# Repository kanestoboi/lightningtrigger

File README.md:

# Lightning Trigger

Features
* Lightning Triggering - By using a photo transistor, lightning strikes are detected and triggers the camera at the same instant.  
  
* Sound Triggering - Sound triggering mode is used to capture sound events such as water droplets, breaking glass, and fireworks.  
  
* Timelapse- Calculates the number of photos for a given length timelapse, given the photo duration, interval, and total timelapse length before taking all the required photos.  
  
Currently has support for two triggering outputs (can trigger two devices at once) with an additional two outputs being added in the next revision.  
  
Control is through an Android app using the HM-11 Bluetooth module.  
  
Power is from a li-po battery and is charged using an onboard li-po charger.

## Images

Images are located in the [Images](https://github.com/kanestoboi/lightningtrigger/tree/master/Images) directory.

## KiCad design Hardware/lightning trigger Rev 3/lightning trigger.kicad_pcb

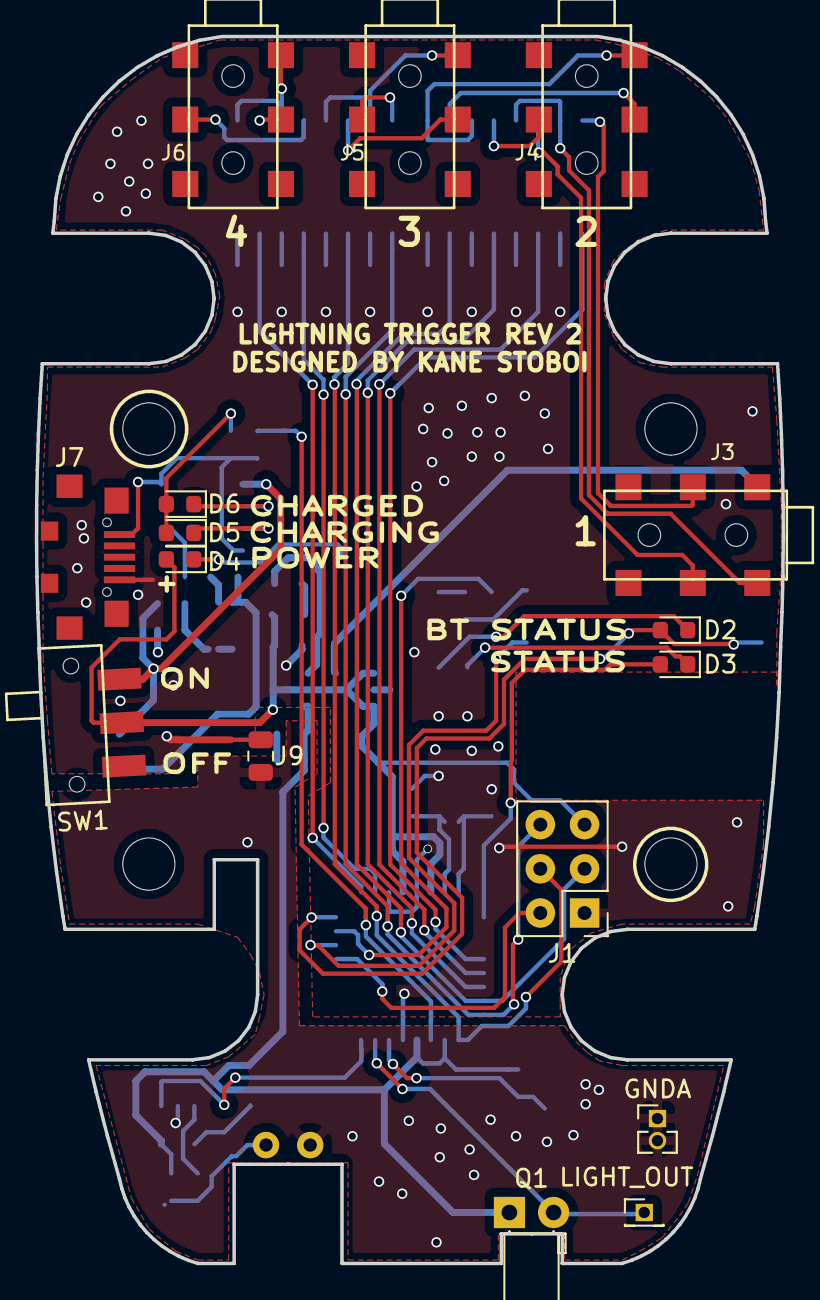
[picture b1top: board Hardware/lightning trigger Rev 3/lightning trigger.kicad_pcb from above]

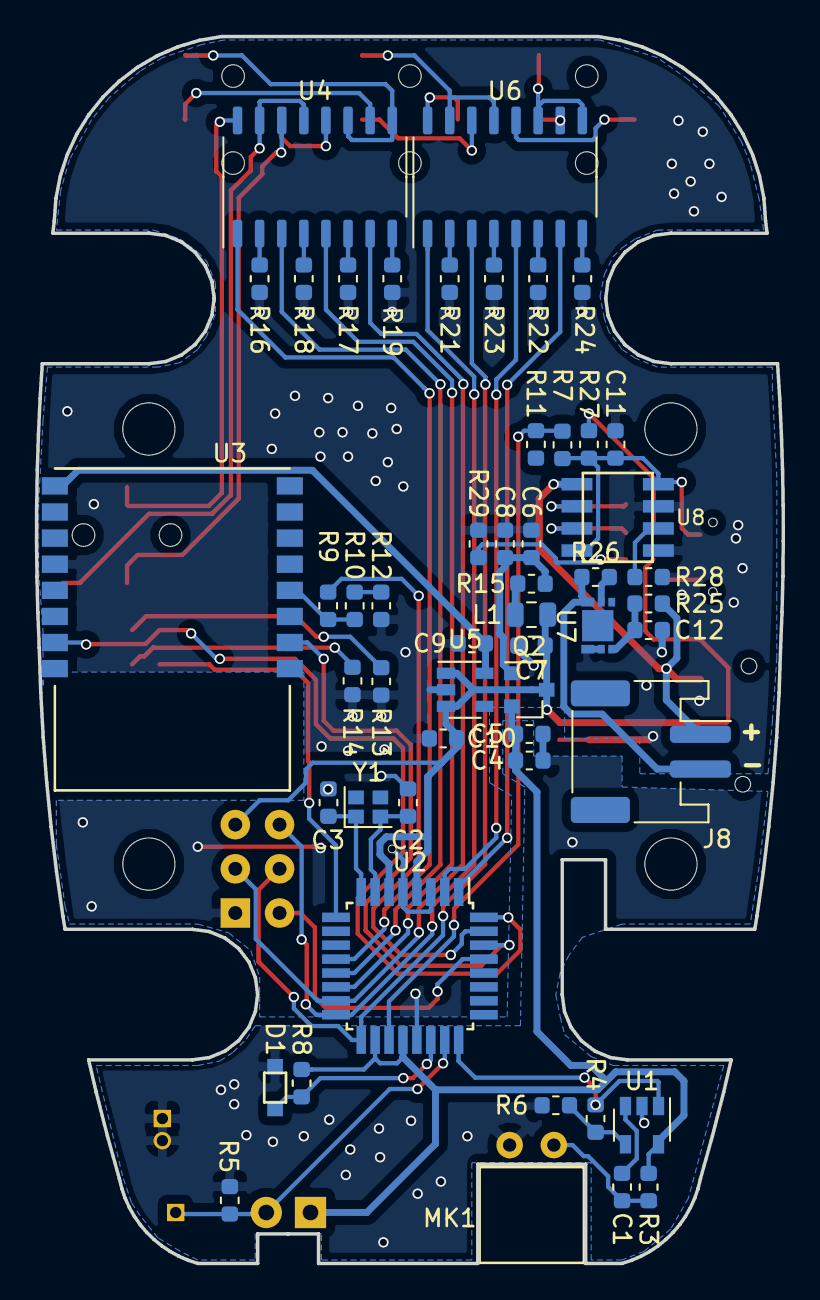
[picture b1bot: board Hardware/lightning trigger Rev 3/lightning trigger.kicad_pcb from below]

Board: 2 copper layers, 42.9 x 70.5 mm, 68 parts (52 on the bottom side), 63 nets.

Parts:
C1, C4, C7, C8, C9, C10, C11, C12: 100nF; C_0603_1608Metric
C2: 10pF; C_0603_1608Metric
C3: 22pF; C_0603_1608Metric
C5, C6: 1nF; C_0603_1608Metric
D1: D_Zener; SC-90A
D2, D3, D4, D5, D6: LED; LED_0603_1608Metric
GNDA: PinHeader_1x02_P1.27mm_Vertical
J1: Conn_02x03_Odd_Even; Pin_Header_Straight_2x03_Pitch2.54mm
J3, J4, J5, J6: SJ-2523-SMT; PJ-237-6A
J7: USB_OTG; USB_Micro_C77238
J8: Conn_01x02_Female; JST_PH_S2B-PH-SM4-TB_1x02-1MP_P2.00mm_Horizontal
J9: Conn_01x02; R_0805_2012Metric
L1: Ferrite_Bead; C_0805_2012Metric
LIGHT_OUT: PinHeader_1x01_P1.27mm_Vertical
MK1: Microphone; ELECTRET MICROPHONE
Q1: Q_Photo_NPN; LED_D3.0mm_Horizontal_O1.27mm_Z2.0mm
Q2: MMBT3904; SOT-23
R3, R5: 10k; R_0603_1608Metric
R4, R6, R16, R17, R18, R19, R21, R22, R23, R24, R25: 150; R_0603_1608Metric
R7, R9, R10, R11, R12, R13, R14, R26, R27, R28, R29: 2k; R_0603_1608Metric
R8: 47; R_0603_1608Metric
R15: 160k; R_0603_1608Metric
SW1: SW_SPDT; JS102011SAQN
U1: MCP6001; SOT-23-5
U2: ATMEGA328P-AU; TQFP-32_7x7mm_Pitch0.8mm
U3: HM-11
U4, U6: TLP291-4; SOIC-16_4.55x10.3mm_P1.27mm
U5: TLV70233_SOT23-5; SOT-23-5
U7: AP9211; U-DFN2030-6
U8: TP4056; SOP-8
Y1: Crystal; Crystal_SMD_2016-4Pin_2.0x1.6mm

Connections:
3.3V: C9.1, U3.9, U5.5
+BATT: J8.1, R25.2, SW1.1, U8.5
-BATT: J8.2, R26.1, U7.6
FOCUS1: U2.13, U4.3
FOCUS2: J1.3, U2.15, U4.7
FOCUS3: J1.4, U2.17, U6.3
FOCUS4: U2.1, U6.7
GNDA: C4.2, C5.2, D1.2, GNDA.1, GNDA.2, J9.2, MK1.1, R5.2, R6.1, U1.2
GNDD: C2.2, C3.2, C6.2, C7.2, C8.2, C9.2, C10.2, C11.2, C12.2, J1.1, J7.5, J9.1, R12.2, R13.1, R14.1, R16.2, R17.2, R18.2, R19.2, R21.2, R22.2, R23.2, R24.2, R28.1, R29.2, U2.3, U2.5, U2.21, U3.12, U5.2, U7.1, U7.2, U8.1, U8.3
LIGHT_OUT: LIGHT_OUT.1, Q1.2, R5.1, U2.23
MICROPHONE_OUT: R4.2, U1.1, U2.24
MISO: J1.6, U2.16, U6.1
unnamed: C1.1, U1.3
unnamed: C1.2, MK1.2, R3.1
unnamed: C2.1, U2.7, Y1.2
unnamed: C3.1, U2.8, Y1.1
unnamed: C6.1, C8.1, Q2.1, R15.1
unnamed: C12.1, R25.1, U7.3
unnamed: D1.1, R8.1, U2.22
unnamed: D2.1, R13.2
unnamed: D2.2, U2.32, U3.15
unnamed: D3.1, R14.2
unnamed: D3.2, U2.9
unnamed: D4.1, R29.1
unnamed: D5.1, U8.7
unnamed: D5.2, D6.2, R27.1
unnamed: D6.1, U8.6
unnamed: J3.1, U4.13, U4.15
unnamed: J3.2, U4.16
unnamed: J3.3, U4.14
unnamed: J4.1, U4.9, U4.11
unnamed: J4.2, U4.12
unnamed: J4.3, U4.10
unnamed: J5.1, U6.13, U6.15
unnamed: J5.2, U6.16
unnamed: J5.3, U6.14
unnamed: J6.1, U6.9, U6.11
unnamed: J6.2, U6.12
unnamed: J6.3, U6.10
unnamed: L1.1, R15.2
unnamed: R4.1, R6.2, U1.4
unnamed: R9.2, U2.31
unnamed: R9.1, R10.1, U3.4
unnamed: R10.2, R12.1
unnamed: R7.2, R11.2, U2.19
unnamed: R16.1, U4.2
unnamed: R17.1, U4.6
unnamed: R18.1, U4.4
unnamed: R19.1, U4.8
unnamed: R21.1, U6.2
unnamed: R22.1, U6.6
unnamed: R23.1, U6.4
unnamed: R24.1, U6.8
unnamed: R26.2, U7.5
unnamed: R28.2, U8.2
unnamed: U2.30, U3.2
RST: J1.2, U2.29
SHUTTER1: U2.12, U4.1
SHUTTER2: U2.14, U4.5
SHUTTER4: U2.2, U6.5
VDDA: C4.1, C5.1, Q1.1, Q2.2, R3.2, R8.2, U1.5, U2.18, U2.20
VIN: C7.1, C10.1, D4.2, J1.5, L1.2, Q2.3, SW1.2, U2.4, U2.6, U5.1, U5.3
VUSB: C11.1, J7.1, R7.1, R27.2, U8.4, U8.8

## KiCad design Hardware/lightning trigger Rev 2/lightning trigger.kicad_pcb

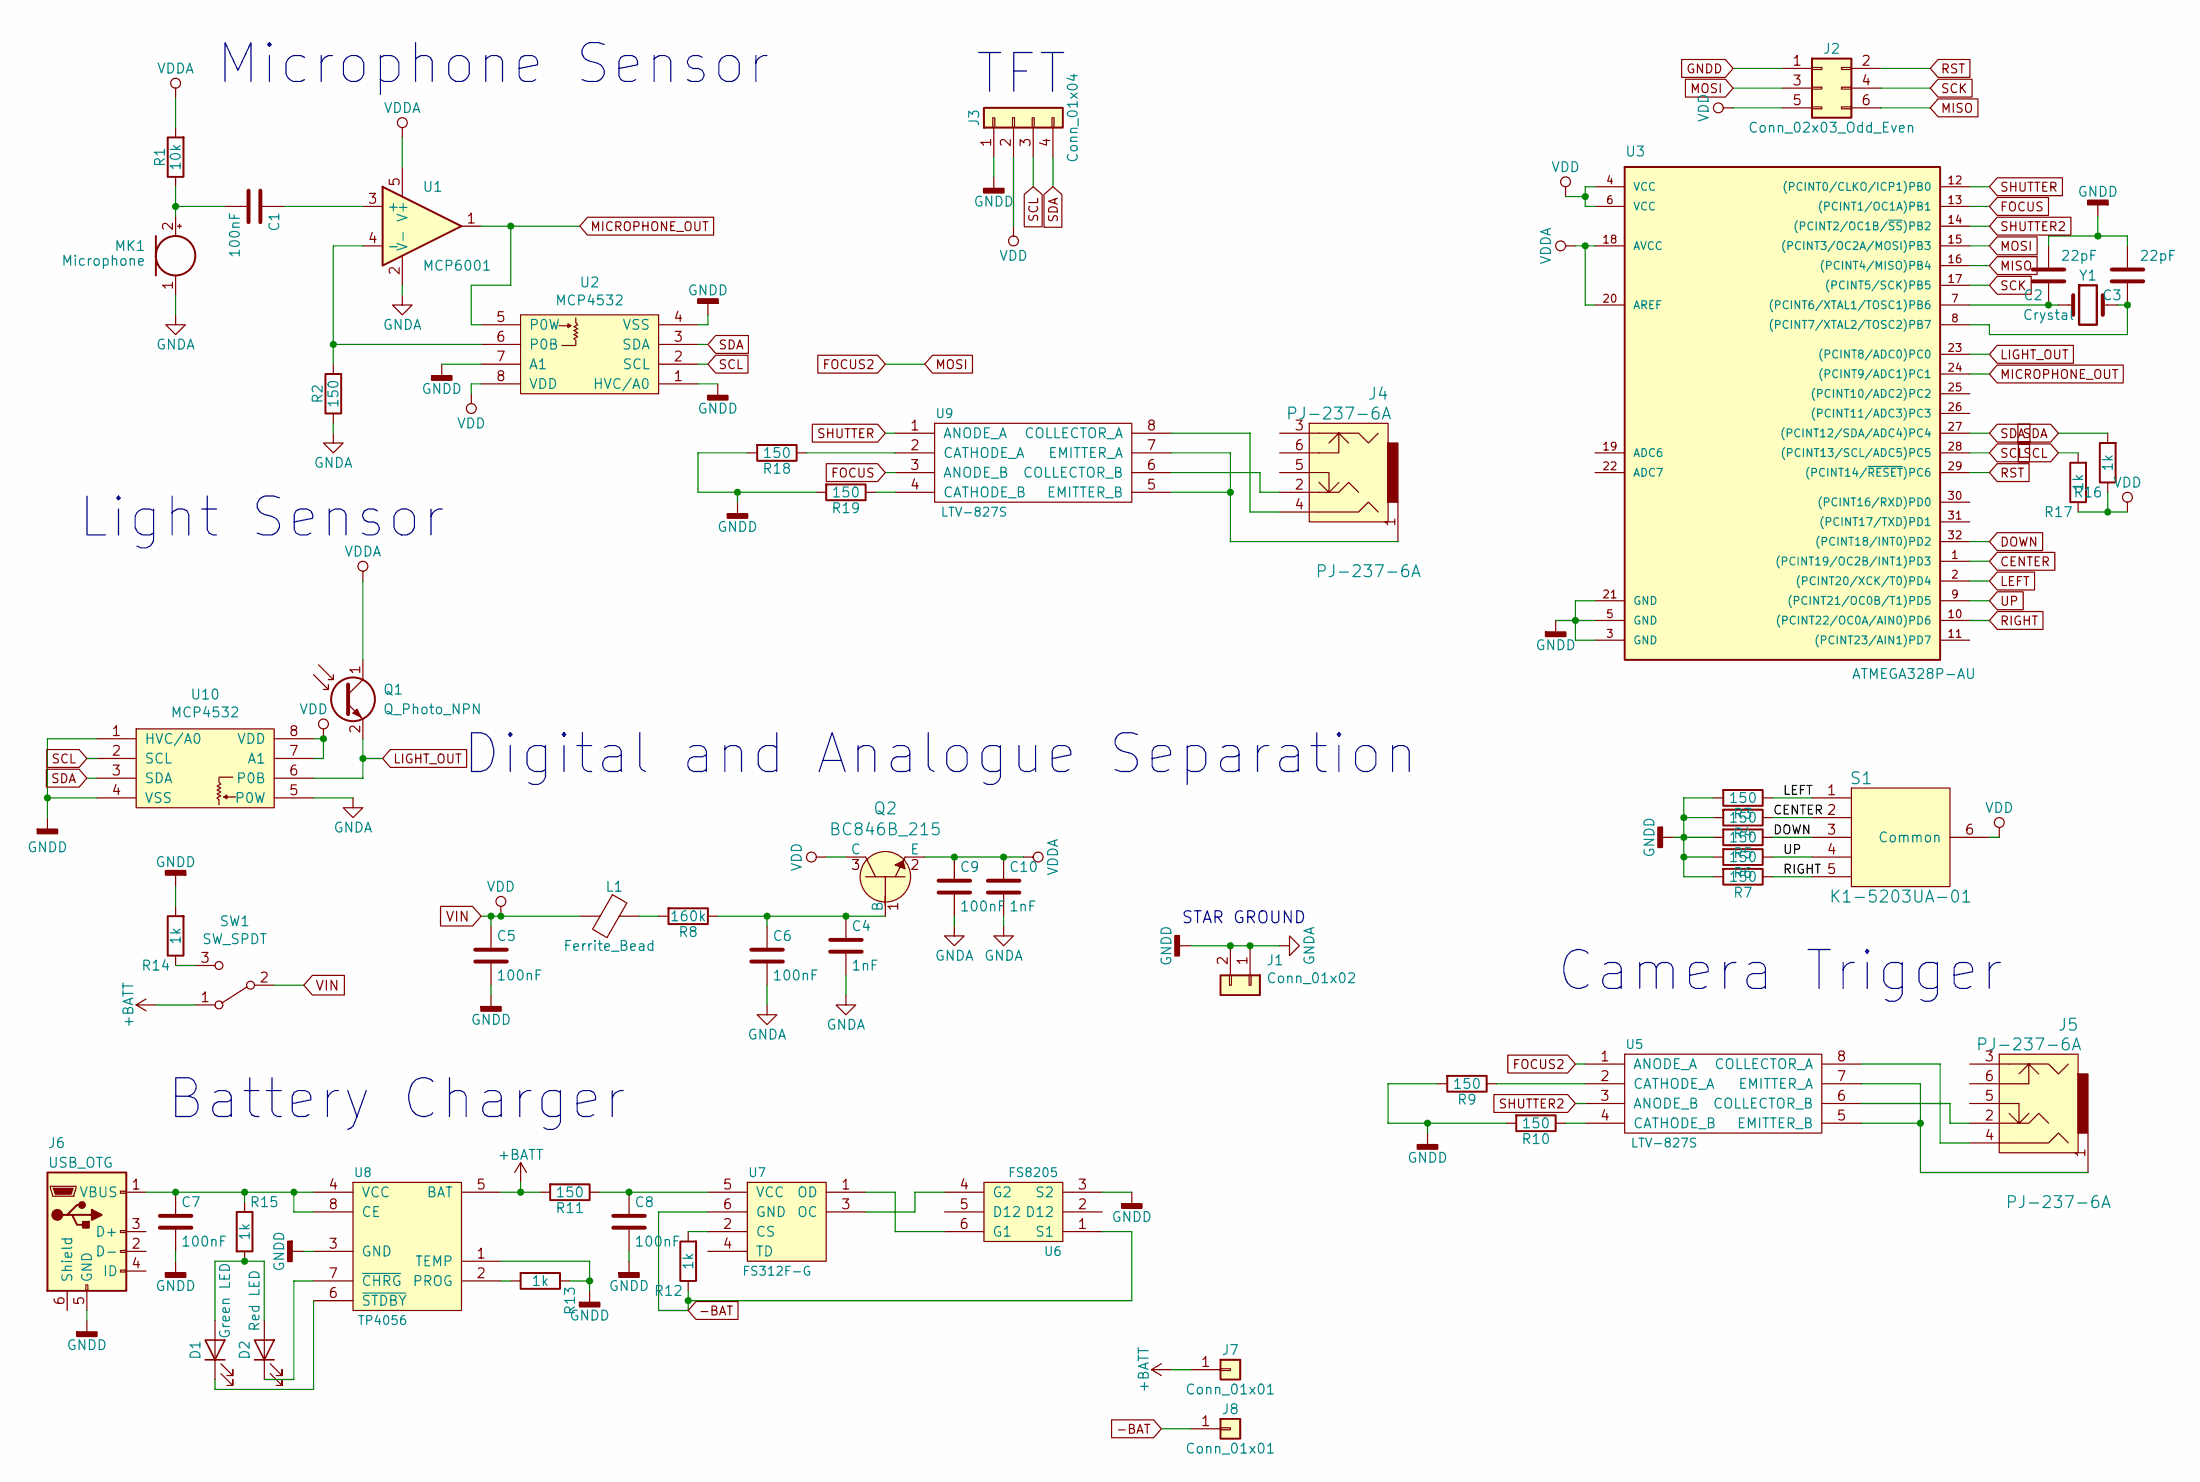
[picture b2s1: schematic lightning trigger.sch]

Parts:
C1, C5, C6, C7, C8, C9: 100nF; C_0805; Manufacturer P/N 0805B104K250
C2, C3: 22pF; C_0805; Manufacturer P/N N/A
C4, C10: 1nF; C_0805; Manufacturer P/N N/A
D1: Green LED; LED_0805; Manufacturer P/N ORH-G35A
D2: Red LED; LED_0805; Manufacturer P/N ORH-R35A
J1: Conn_01x02; PinHeader_1x02_P1.00mm_Vertical
J2: Conn_02x03_Odd_Even; Pin_Header_Straight_2x03_Pitch2.54mm
J3: Conn_01x04; Pin_Header_Straight_1x04_Pitch2.54mm
J4, J5: PJ-237-6A; Manufacturer P/N PJ-237-6A
J6: USB_OTG; USB_Micro_C77238; Manufacturer P/N N/A
J7, J8: Conn_01x01; Pin_Header_Straight_1x01_Pitch2.54mm
L1: Ferrite_Bead; C_0805; Manufacturer P/N MH2029-300Y
MK1: Microphone; Pin_Header_Angled_1x02_Pitch2.54mm; Manufacturer P/N N/A
Q1: Q_Photo_NPN; LED_D3.0mm_Horizontal_O1.27mm_Z2.0mm; Manufacturer P/N SFH 310-2/3
Q2: BC846B_215; SOT-23-3; MPN BC846B,215; Digi-Key_PN 1727-2920-1-ND
R1: 10k; R_0805_2012Metric; Manufacturer P/N RMCF0805FT10K0
R2, R9, R10, R11, R18, R19: 150; R_0805_2012Metric; Manufacturer P/N RNCP0603FTD150R
R3, R4, R5, R6, R7: 150; R_0805_2012Metric
R8: 160k; R_0805_2012Metric; Manufacturer P/N ERJ-6ENF1603V
R12, R13, R14, R15, R16, R17: 1k; R_0805_2012Metric; Manufacturer P/N RS-05K1001FT
S1: K1-5203UA-01; Manufacturer P/N K1-5203UA-01
SW1: SW_SPDT; JS102011SAQN; Manufacturer P/N JS102011SAQN
U1: MCP6001; SOT-23-5; Manufacturer P/N MCP6001T-I/OT
U2, U10: MCP4532; 8-MSOP; Manufacturer P/N MCP4532T-103E/MS
U3: ATMEGA328P-AU; TQFP-32_7x7mm_Pitch0.8mm; Manufacturer P/N ATMEGA328P-AU
U5, U9: LTV-827S; LTV-827S-TA1; Manufacturer P/N LTV-827S-TA1
U6: FS8205; SOT-23-6; Manufacturer P/N FS8205
U7: FS312F-G; SOT-23-6; Manufacturer P/N FS312F-G
U8: TP4056; SOP-8; Manufacturer P/N TP4056
Y1: Crystal; Crystal_HC18-U_Vertical; Manufacturer P/N N/A

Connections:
+BATT: J7.1, R11.2, SW1.1 (A), U8.5 (BAT)
-BAT: J8.1, R12.1, U6.1 (S1), U7.6 (GND)
CENTER: R4.1, S1.2, U3.1 ((PCINT19/OC2B/INT1)PD3)
DOWN: R5.1, S1.3, U3.32 ((PCINT18/INT0)PD2)
FOCUS: U3.13 ((PCINT1/OC1A)PB1), U9.3 (ANODE_B)
FOCUS2: J2.3, U3.15 ((PCINT3/OC2A/MOSI)PB3), U5.1 (ANODE_A)
GNDD: C2.2, C3.2, C4.2, C5.2, C6.2, C7.2, C8.2, C9.2, C10.2, J1.1, J1.2, J2.1, J3.1, J6.5 (GND), MK1.1 (-), R2.1, R3.2, R4.2, R5.2, R6.2, R7.2, R9.2, R10.2, R13.1, R14.2, R18.2, R19.2, U1.2 (V-), U2.1 (HVC/A0), U2.4 (VSS), U2.7 (A1), U3.3 (GND), U3.5 (GND), U3.21 (GND), U6.3 (S2), U8.1 (TEMP), U8.3 (GND), U10.1 (HVC/A0), U10.4 (VSS), U10.5 (P0W)
LEFT: R3.1, S1.1, U3.2 ((PCINT20/XCK/T0)PD4)
LIGHT_OUT: Q1.2 (E), U3.23 ((PCINT8/ADC0)PC0), U10.6 (P0B)
MICROPHONE_OUT: U1.1, U2.5 (P0W), U3.24 ((PCINT9/ADC1)PC1)
MISO: J2.6, U3.16 ((PCINT4/MISO)PB4)
unnamed: C1.1, U1.3 (+)
unnamed: C1.2, MK1.2 (+), R1.1
unnamed: C2.1, U3.7 ((PCINT6/XTAL1/TOSC1)PB6), Y1.1
unnamed: C3.1, U3.8 ((PCINT7/XTAL2/TOSC2)PB7), Y1.2
unnamed: C4.1, C6.1, Q2.1 (B), R8.1
unnamed: C7.1, J6.1 (VBUS), R15.1, U8.4 (VCC), U8.8 (CE)
unnamed: C8.1, R11.1, U7.5 (VCC)
unnamed: D1.1 (K), U8.6 (~STDBY)
unnamed: D1.2 (A), D2.2 (A), R15.2
unnamed: D2.1 (K), U8.7 (~CHRG)
unnamed: J4.1, U9.5 (EMITTER_B), U9.7 (EMITTER_A)
unnamed: J4.2, U9.6 (COLLECTOR_B)
unnamed: J4.4, U9.8 (COLLECTOR_A)
unnamed: J5.1, U5.5 (EMITTER_B), U5.7 (EMITTER_A)
unnamed: J5.2, U5.6 (COLLECTOR_B)
unnamed: J5.4, U5.8 (COLLECTOR_A)
unnamed: L1.1, R8.2
unnamed: R2.2, U1.4 (-), U2.6 (P0B)
unnamed: R9.1, U5.2 (CATHODE_A)
unnamed: R10.1, U5.4 (CATHODE_B)
unnamed: R12.2, U7.2 (CS)
unnamed: R13.2, U8.2 (PROG)
unnamed: R14.1, SW1.3 (C)
unnamed: R18.1, U9.2 (CATHODE_A)
unnamed: R19.1, U9.4 (CATHODE_B)
unnamed: U6.4 (G2), U7.3 (OC)
unnamed: U6.6 (G1), U7.1 (OD)
RIGHT: R7.1, S1.5, U3.10 ((PCINT22/OC0A/AIN0)PD6)
RST: J2.2, U3.29 ((PCINT14/~RESET~)PC6)
SCK: J2.4, U3.17 ((PCINT5/SCK)PB5)
SCL: J3.3, R17.2, U2.2 (SCL), U3.28 ((PCINT13/SCL/ADC5)PC5), U10.2 (SCL)
SDA: J3.4, R16.2, U2.3 (SDA), U3.27 ((PCINT12/SDA/ADC4)PC4), U10.3 (SDA)
SHUTTER: U3.12 ((PCINT0/CLKO/ICP1)PB0), U9.1 (ANODE_A)
SHUTTER2: U3.14 ((PCINT2/OC1B/~SS~)PB2), U5.3 (ANODE_B)
UP: R6.1, S1.4, U3.9 ((PCINT21/OC0B/T1)PD5)
VDDA: C9.1, C10.1, Q1.1 (C), Q2.2 (E), R1.2, U1.5 (V+), U3.18 (AVCC), U3.20 (AREF)
VIN: C5.1, J2.5, J3.2, L1.2, Q2.3 (C), R16.1, R17.1, S1.6 (Common), SW1.2 (B), U2.8 (VDD), U3.4 (VCC), U3.6 (VCC), U10.7 (A1), U10.8 (VDD)

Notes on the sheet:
Microphone Sensor
Light Sensor
Camera Trigger
TFT
Battery Charger
Digital and Analogue Separation
STAR GROUND

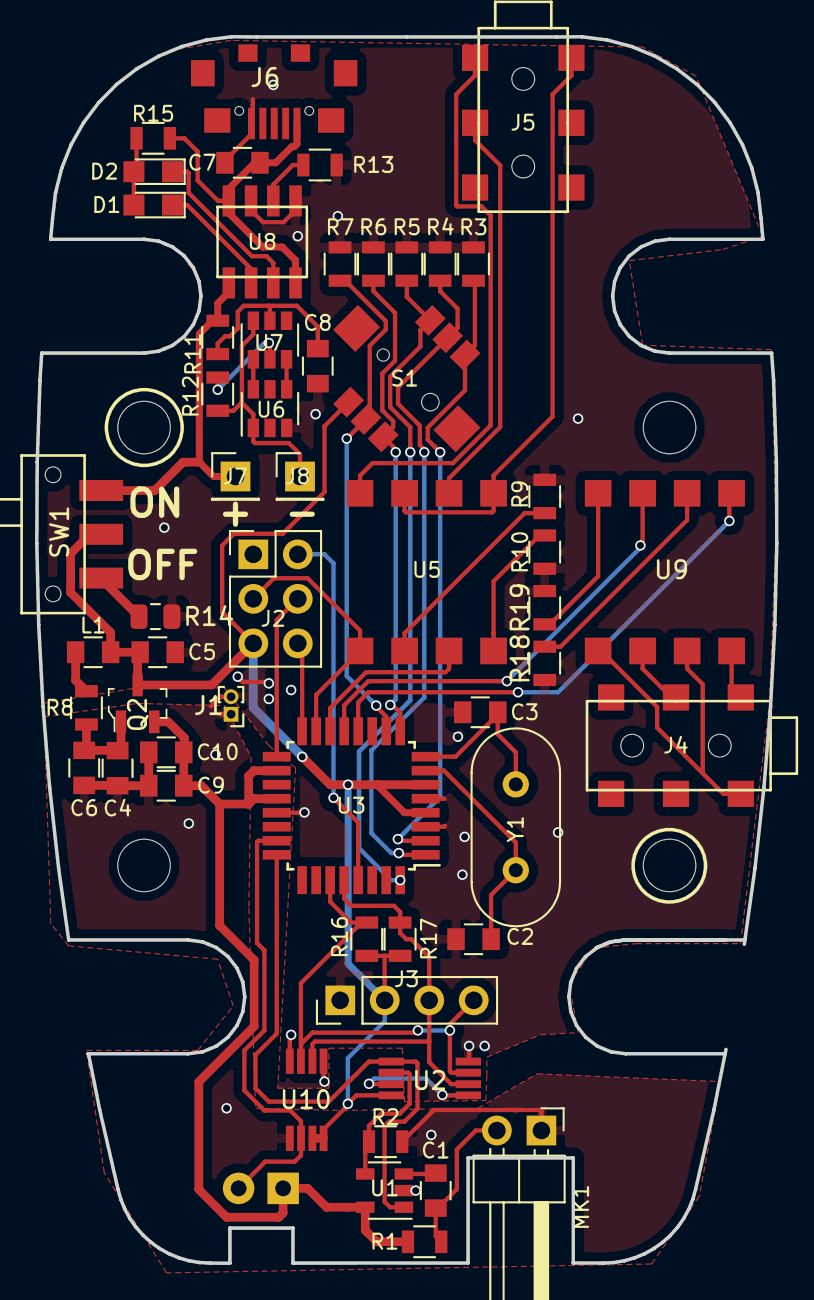
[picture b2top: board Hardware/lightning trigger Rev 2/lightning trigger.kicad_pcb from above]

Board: 2 copper layers, 42.2 x 70.0 mm, 55 parts (1 on the bottom side), 48 nets.

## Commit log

2019-01-29 added to-to and tasks
2019-01-29 added .gitignore file
2019-01-29 added more tasks to list
2019-01-29 added task to list
2019-02-10 added enclosure outline to pcb layout
2019-02-15 added additional tasks to to0to
2019-02-15 added compliance testing to tasks
2019-02-15 re-drew board outline to make it larger
2019-02-15 updated BOM details for parts
2019-02-15 updated footprints for new KiCAD library
2019-02-22 created pdf of schematic
2019-03-01 Added basic sound a lightning triggering functionality
2019-03-02 added trigger comparisons
2019-03-02 updated progress
2019-03-02 refactored ADC conversion code
2019-03-02 added pluto and miops trigger manuals
2019-03-02 added key press detection
2019-03-03 added state machine for menu system. Software is ready for testing on prototype
2019-03-03 more updates to task progress
2019-03-03 restructured hardware files for new revision
2019-03-03 updated git ignore
2019-03-09 fixed bug that would restrict ADC sampling rate (| when setting ADCSRA), added basic calibration of threshold, fixed address of digital potentiometers,
2019-03-09 added more things to fix after working with first revision prototype
2019-03-10 Initial commit of Android app
2019-03-10 Working android app new initial commit
2019-03-10 added error message for when trying to control trigger without bluetooth connected
2019-03-10 changed default status tp not connected
2019-03-17 updated to-do with more changes
2019-03-17 added updating threshold feature
2019-03-17 cleaning up calibration each time an ADC is read
2019-04-11 calibrating each time there is a trigger
2019-04-11 moved transition defining to a separate function. Added flash triggering on sound mode
2019-04-12 sound mode now configured to trigger flash and have camera in bulb mode.
2019-04-13 updating resistors and capacitors to be macrofab house parts
2019-04-13 cashe update
2019-04-13 more schematic updates with new components
2019-04-14 moving microcontroller code new folder
2019-04-15 creating simple bluetooth example using an interrupt to check for a message
2019-04-15 adding bluetooth to lightning trigger code
2019-04-16 adding time-lapse object
2019-04-16 starting to implement time-lapse into main trigger file
2019-04-17 more updated to timelapse mode
2019-04-18 added battery monitor circuitry, and power mux for switching between charging and battery power
2019-04-18 more schematic updates for power mux
2019-04-18 more updates to timelapse mode
2019-04-19 cleaning up time-lapse class
2019-04-19 moved threshold triggering to a new class
2019-04-20 cleaning up arduino code after thresholdTrigger addition
2019-04-21 cleaning up ThresholdTrigger Class
2019-04-21 added BatteryInicator class to monitor battery level
2019-04-21 only add unique bluetooth devices to list
2019-04-21 added datasheet for HM-11
2019-04-22 fixed bug in BatteryIndicator class causing the ADC registers to not be set the same as they were before battery ADC conversion
2019-04-22 updating tasks
2019-04-22 added logic conversion for HM-11 RX module
2019-04-23 additions to sounds triggering
2019-04-23 more additions to sound trigger. Fixed bug in ThresholdTrigger.setup() causing ADCMUX to always be set to input 0
2019-04-23 updating Timelapse class name
2019-04-23 moving triggering variables to be global
2019-04-23 removing blank lines
2019-04-24 adding AT commands file
2019-04-26 correcting formatting of member variables and functions
2019-04-26 adding HDR class
2019-04-26 more changes to rev 2 schematic
2019-04-26 focus camera when in lightning mode
2019-04-27 removed focus command out of run function
2019-04-27 Changed bluetoothRxMessage to be a String object so that full strings can be read from bluetooth. Added adjustable HDR center and exposure values
2019-05-11 updates for json bluetooth message format
2019-05-11 removing hdr development code
2019-05-11 more additions to hdr mode
2019-05-11 updates to trigger threshold
2019-05-11 updated for HM-11
2019-05-11 no message
2019-06-23 Finished revision 2 of board layout
2019-06-23 updates to HDR mode
2019-06-23 threshold trigger updates for bluetooth
2019-06-28 new board outline
2019-06-28 archiving rev 2
2019-06-28 adding support for charging indicator
2019-06-28 set camera to be focused ready for next photo
2019-06-28 updates to support rev 2 board
2019-06-28 new board outline files
2019-06-28 removing gerbers from git
2019-06-28 todo for rev 3
2019-06-28 moving directory to rev 3
2019-07-01 work continuing on rev 2 software updates
2019-07-21 changed from using softwareserial to hardware serial
2019-07-21 adding basic single shot mode
2019-07-21 removed old hardware sensitivity adjustment and Wire code. Added some basic status LED indications when modes are entered and exited.
2019-07-21 updates to work done and new tasks
2019-07-21 optimising DFM. removed 150 ohm resistors and replaced with 2k that are already in use. Added hardware to reset uC from HM-11. Fixed BATT- and GND issue with AP9211 that was causing the battery to st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
2019-07-21 ignoring older uncompressed revisions
2019-09-13 added single shot mode and fixed bug causing currentMode variable to become null. (made variable const char*)
2021-01-09 updated timelapse
2021-02-24 added images
2021-02-24 Create README.md
    added readme
2021-02-24 updated photos
